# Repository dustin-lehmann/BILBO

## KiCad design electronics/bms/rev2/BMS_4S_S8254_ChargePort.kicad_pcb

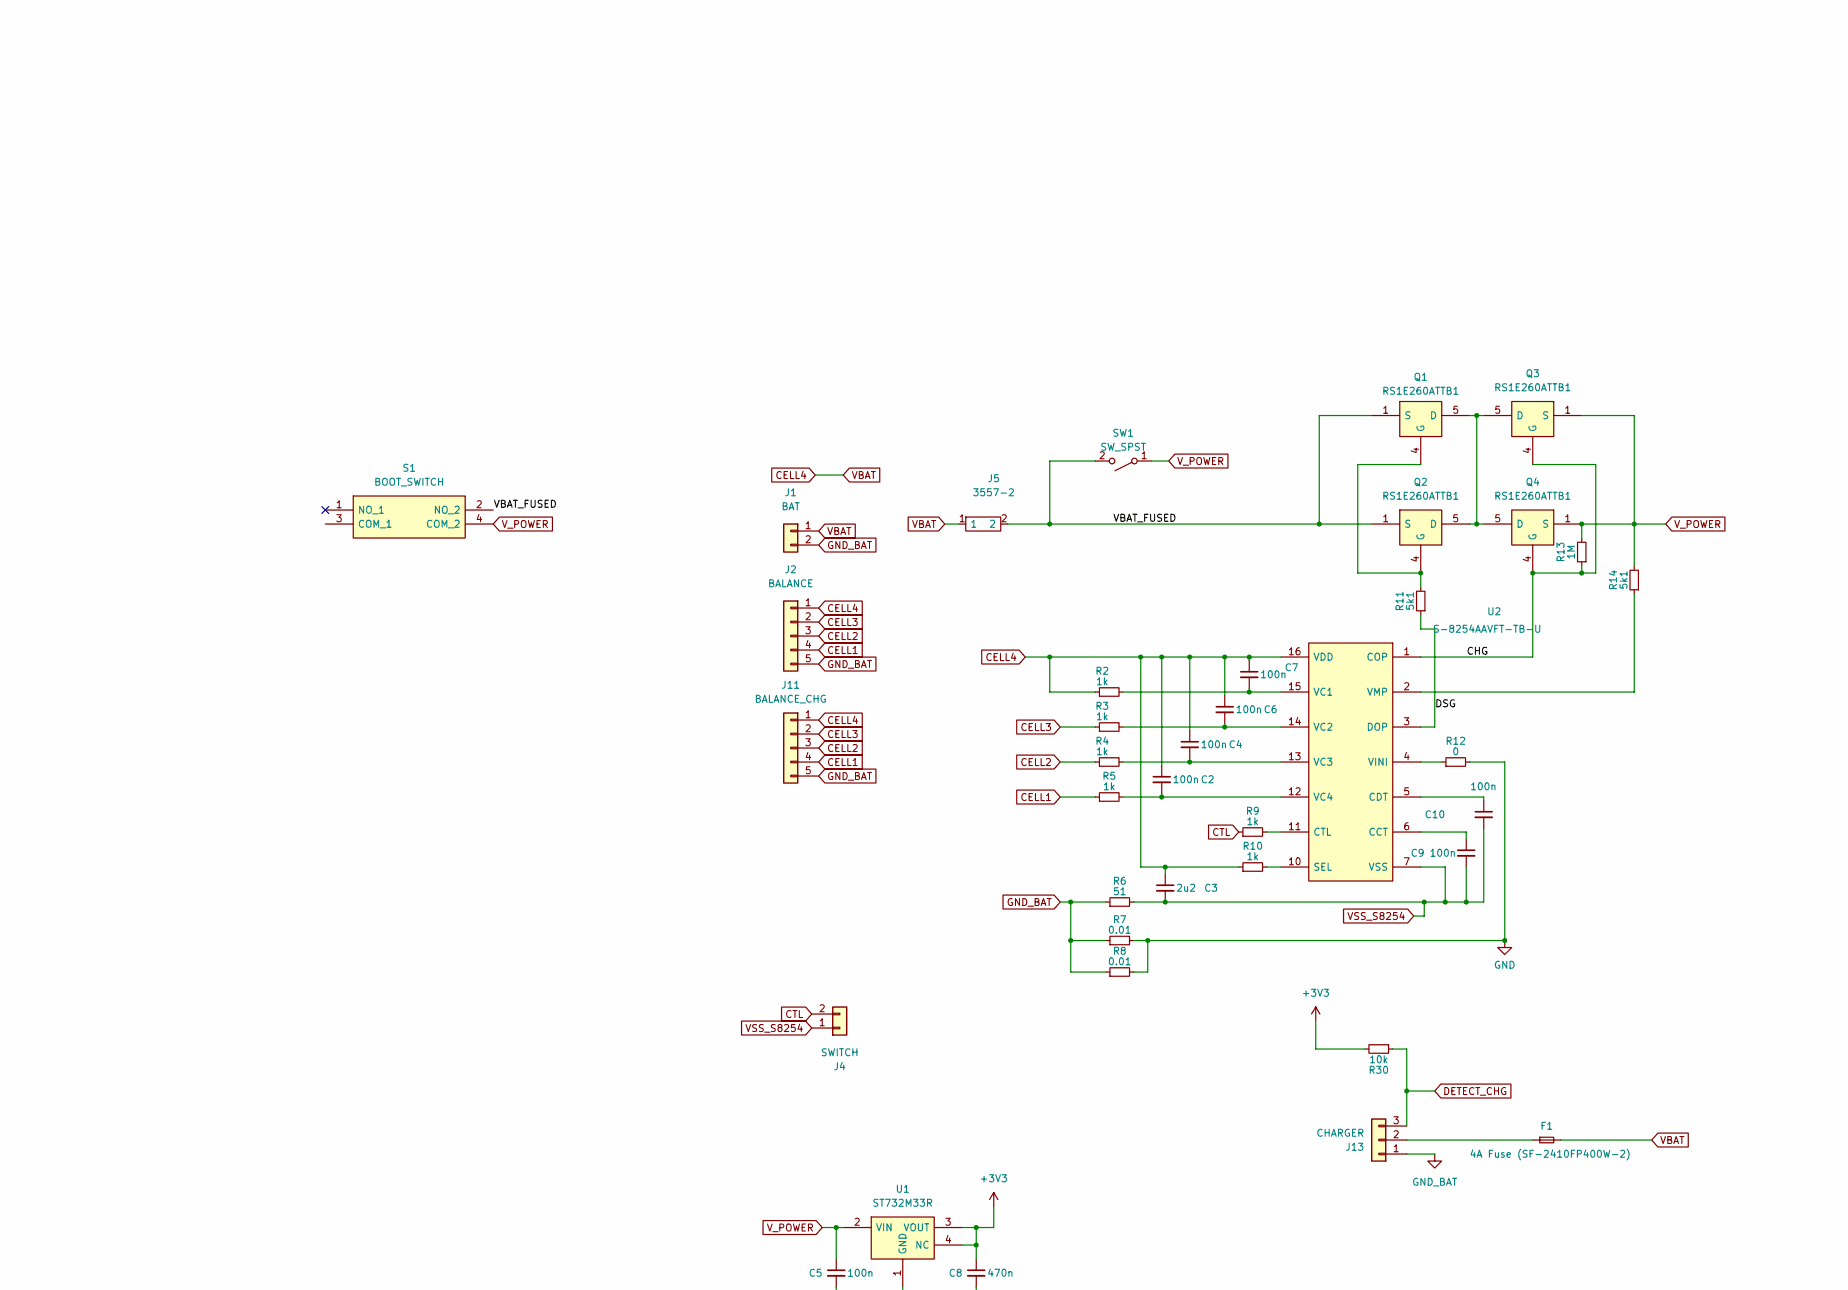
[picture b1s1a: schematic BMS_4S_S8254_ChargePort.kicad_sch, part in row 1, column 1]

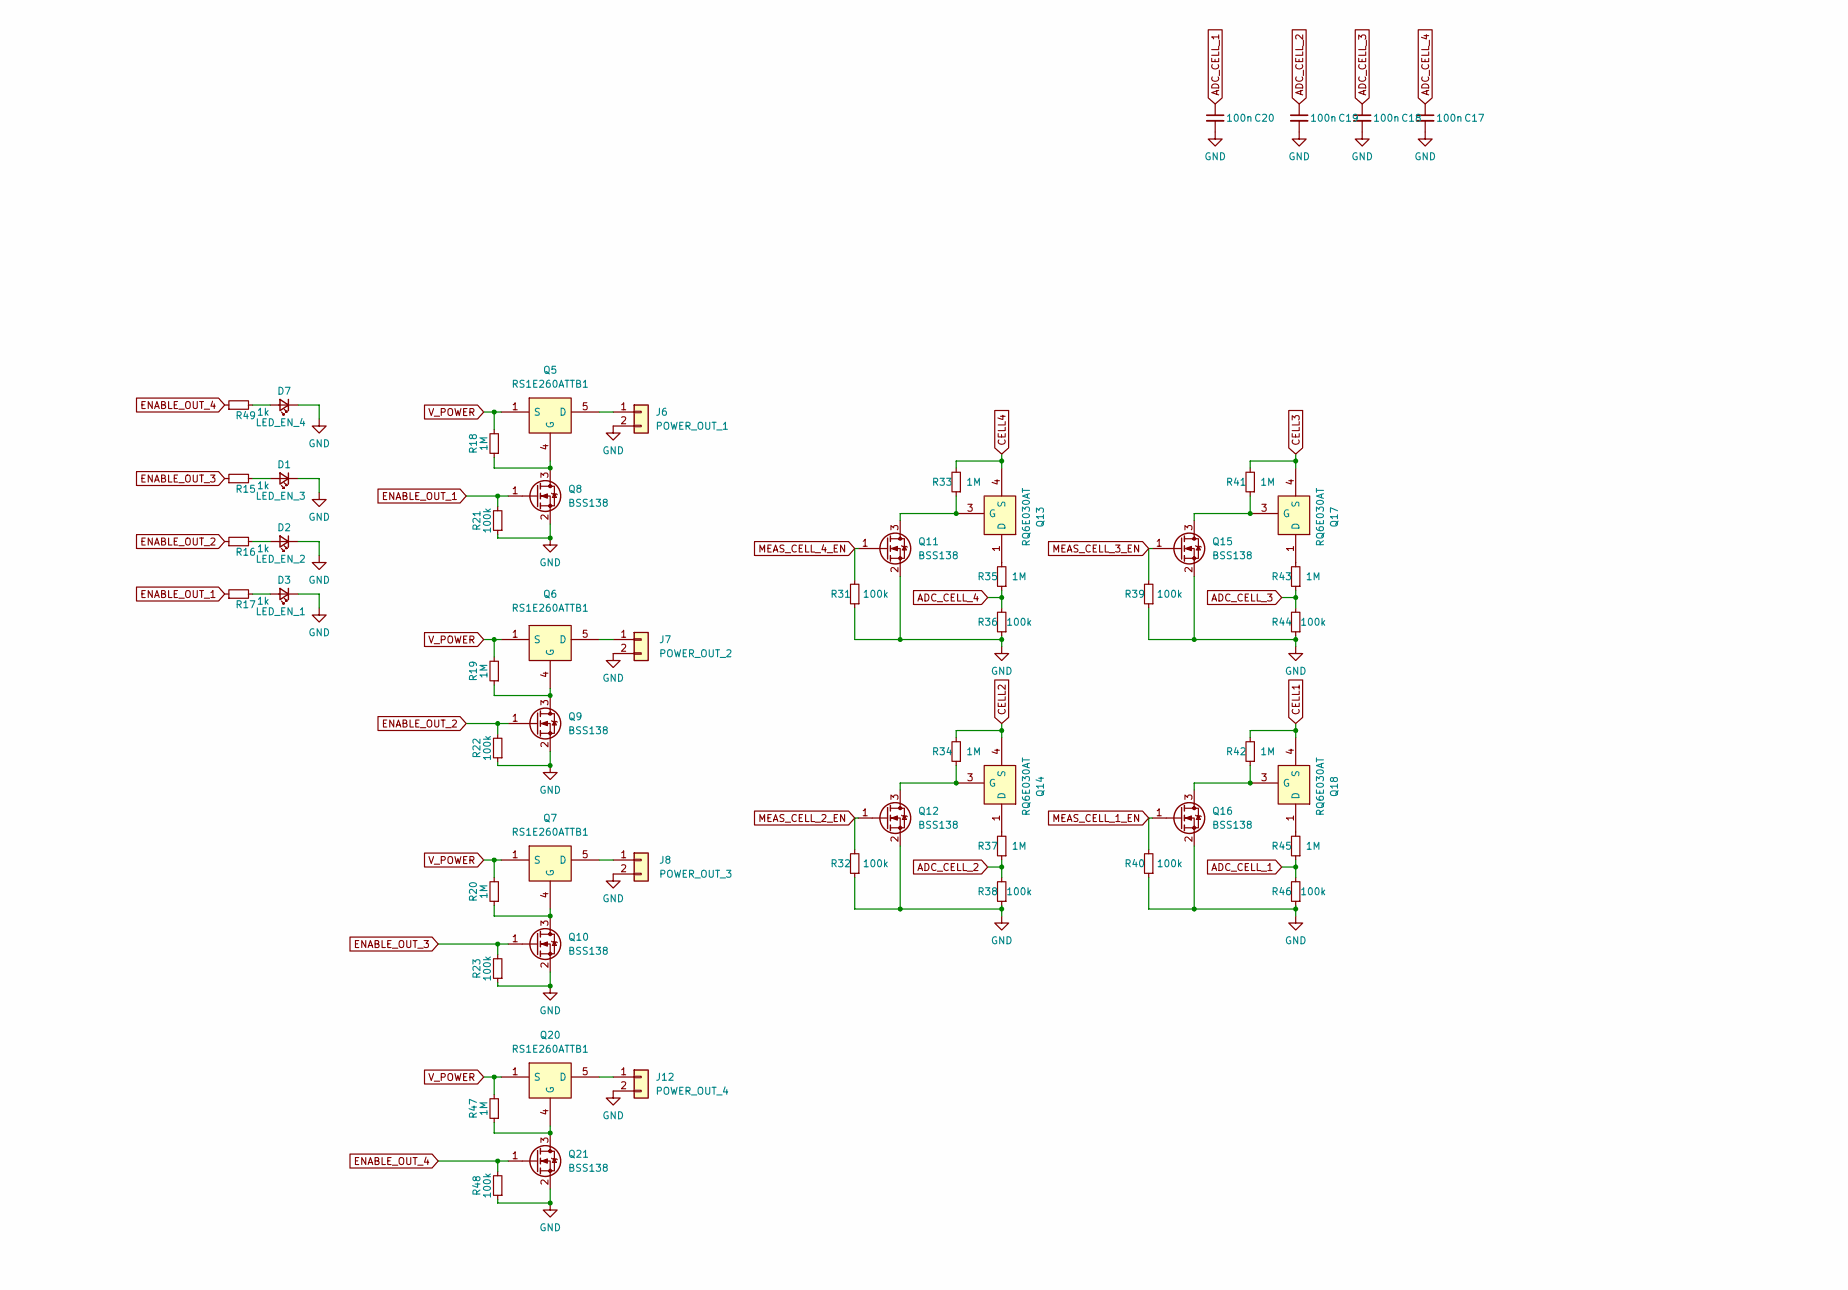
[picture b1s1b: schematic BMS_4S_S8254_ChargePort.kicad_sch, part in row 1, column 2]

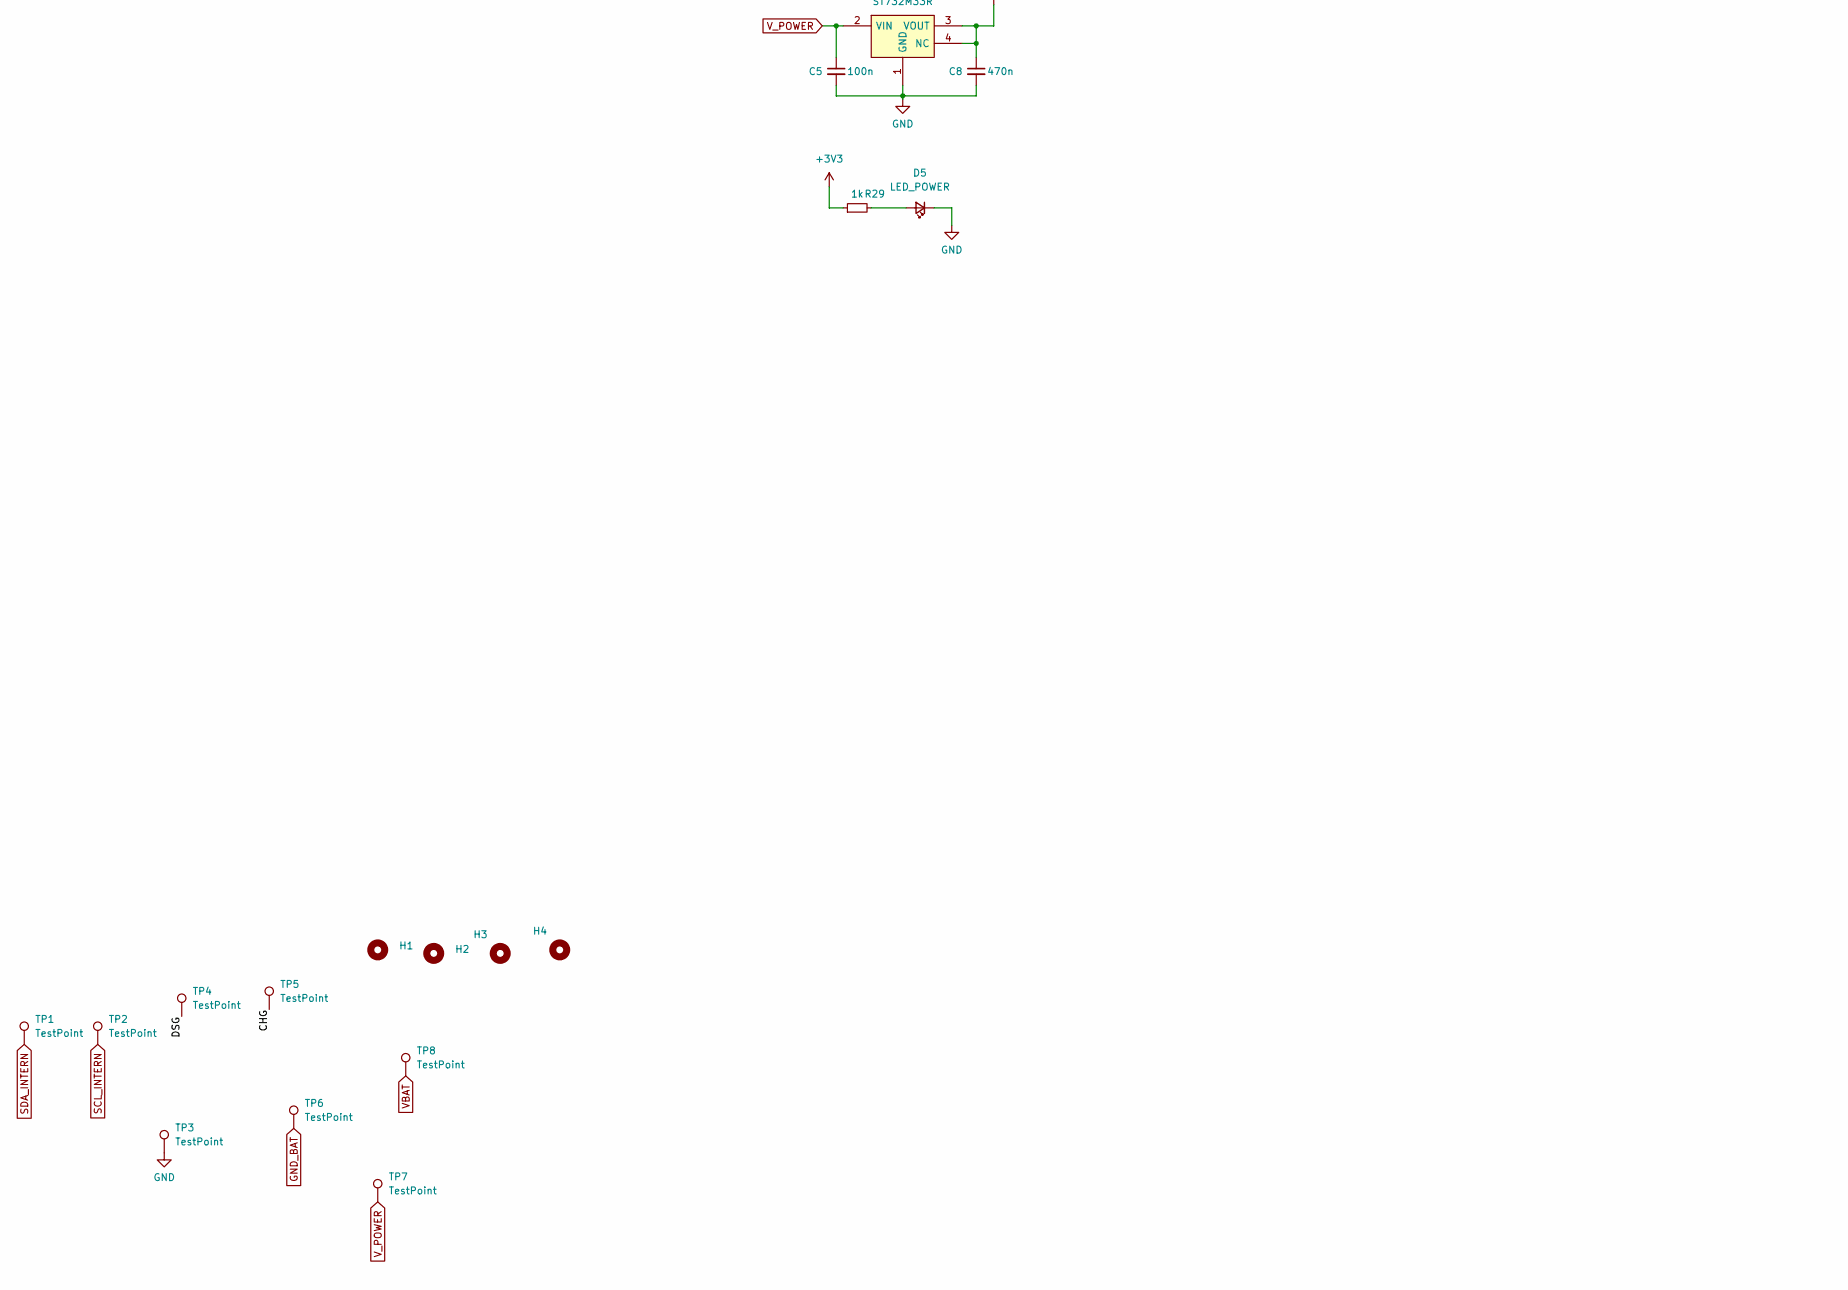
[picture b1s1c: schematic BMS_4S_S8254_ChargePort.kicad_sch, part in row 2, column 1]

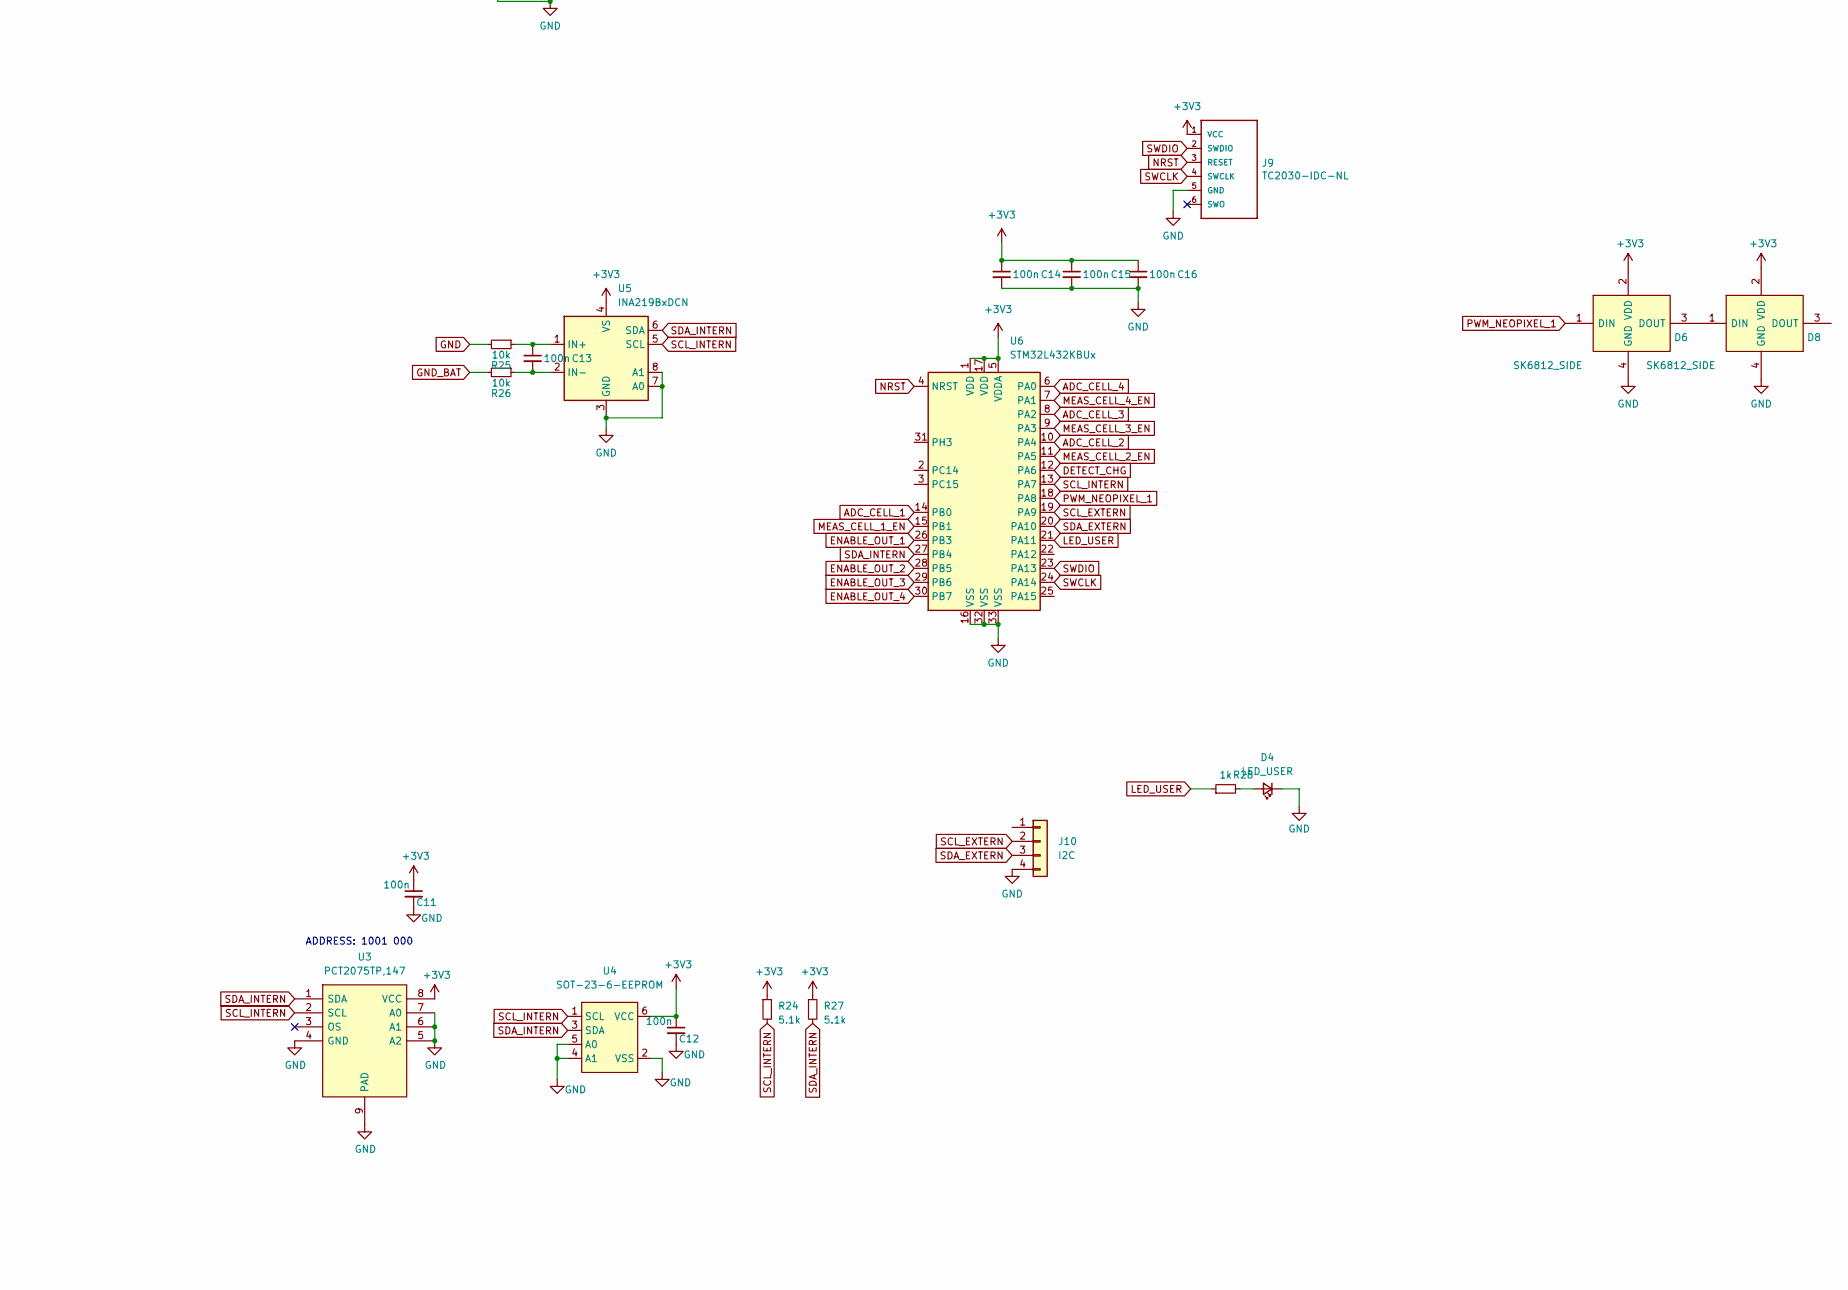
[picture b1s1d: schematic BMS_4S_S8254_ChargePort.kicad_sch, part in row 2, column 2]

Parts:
C2, C4, C5, C6, C7, C9, C10, C11, C12, C13, C14, C15, C16, C17, C18, C19, C20: 100n; C_0603_1608Metric
C3: 2u2; C_0805_2012Metric
C8: 470n; C_0603_1608Metric
D1: LED_EN_3; LED_0603_1608Metric
D2: LED_EN_2; LED_0603_1608Metric
D3: LED_EN_1; LED_0603_1608Metric
D4: LED_USER; LED_0603_1608Metric
D5: LED_POWER; LED_0603_1608Metric
D6, D8: SK6812_SIDE; SK6812SIDE; Manufacturer_Part_Number SK6812 SIDE
D7: LED_EN_4; LED_0603_1608Metric
F1: 4A Fuse (SF-2410FP400W-2); R_2512_6332Metric
H1, H2, H3, H4: MH_noPad_2.5
J1: BAT; AMASS_XT60PW-M
J2: BALANCE; JST_XH_S5B-XH-A_1x05_P2.50mm_Horizontal
J4: SWITCH; JST_GH_BM02B-GHS-TBT_1x02-1MP_P1.25mm_Vertical
J5: 3557-2; Mouser Part Number 534-3557-2
J6: POWER_OUT_1; 691322110002
J7: POWER_OUT_2; 691322110002
J8: POWER_OUT_3; 691322110002
J9: TC2030-IDC-NL; Tag-Connect_TC2030-IDC-NL_2x03_P1.27mm_Vertical
J10: I2C; JST_GH_BM04B-GHS-TBT_1x04-1MP_P1.25mm_Vertical
J11: BALANCE_CHG; JST_XH_S5B-XH-A_1x05_P2.50mm_Horizontal
J12: POWER_OUT_4; 691322110002
J13: CHARGER; AMASS_XT60IPW-M_1x03_P7.20mm_Horizontal
Q1, Q2, Q3, Q4, Q5, Q6, Q7, Q20: RS1E260ATTB1; Mouser Part Number 755-RS1E260ATTB1
Q8, Q9, Q10, Q11, Q12, Q15, Q16, Q21: BSS138; SOT-323_SC-70
Q13, Q14, Q17, Q18: RQ6E030AT; SOT95P280X100-6N; Mouser Part Number 755-RZQ045P01TR
R2, R3, R4, R5, R9, R10, R15, R16, R17, R28, R29, R49: 1k; R_0603_1608Metric
R6: 51; R_0603_1608Metric
R7, R8: 0.01; R_2512_6332Metric
R11, R14: 5k1; R_0603_1608Metric
R12: 0; R_0603_1608Metric
R13, R18, R19, R20, R33, R34, R35, R37, R41, R42, R43, R45, R47: 1M; R_0603_1608Metric
R21, R22, R23, R31, R32, R36, R38, R39, R40, R44, R46, R48: 100k; R_0603_1608Metric
R24, R27: 5.1k; R_0603_1608Metric
R25, R26, R30: 10k; R_0603_1608Metric
S1: BOOT_SWITCH; EVQPUA02K; Manufacturer_Part_Number 434123025826
SW1: SW_SPST; JST_GH_BM02B-GHS-TBT_1x02-1MP_P1.25mm_Vertical
TP1, TP2, TP3, TP4, TP5, TP6, TP7, TP8: TestPoint; TestPoint_Pad_D1.5mm
U1: ST732M33R; SOT95P280X145-5N; Mouser Part Number 511-ST732M33R
U2: S-8254AAVFT-TB-U; SOP65P640X110-16N; Mouser Part Number 628-S-8254AAVFT-TB-G
U3: PCT2075TP,147; SON50P300X200X80-9N; Mouser Part Number 771-PCT2075TP147
U4: SOT-23-6-EEPROM; SOT-23-6
U5: INA219BxDCN; SOT-23-8
U6: STM32L432KBUx; QFN-32-1EP_5x5mm_P0.5mm_EP3.45x3.45mm

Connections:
+3V3: C8.1, C11.1, C12.1, C14.1, C15.1, C16.1, D6.2 (VDD), D8.2 (VDD), J9.1 (VCC), R24.1, R27.1, R29.1, R30.2, U1.3 (VOUT), U1.4 (NC), U3.8 (VCC), U4.6 (VCC), U5.4 (VS), U6.1 (VDD), U6.5 (VDDA), U6.17 (VDD)
/CHG: Q3.4 (G), Q4.4 (G), R13.1, TP5.1, U2.1 (COP)
/DSG: R11.1, TP4.1, U2.3 (DOP)
/VBAT_FUSED: J5.2, J5.4, Q1.1 (S), Q1.2 (S), Q1.3 (S), Q2.1 (S), Q2.2 (S), Q2.3 (S), S1.2 (NO_2), SW1.2 (B)
ADC_CELL_1: C20.1, R45.1, R46.2, U6.14 (PB0)
ADC_CELL_2: C19.1, R37.1, R38.2, U6.10 (PA4)
ADC_CELL_3: C18.1, R43.1, R44.2, U6.8 (PA2)
ADC_CELL_4: C17.1, R35.1, R36.2, U6.6 (PA0)
CELL1: J2.4, J11.4, Q18.4 (S), R5.1, R42.2
CELL2: J2.3, J11.3, Q14.4 (S), R4.1, R34.2
CELL3: J2.2, J11.2, Q17.4 (S), R3.1, R41.2
CELL4: C2.1, C3.1, C4.1, C6.1, C7.1, F1.2, J1.1, J2.1, J5.1, J5.3, J11.1, Q13.4 (S), R2.1, R10.1, R33.2, TP8.1, U2.16 (VDD)
CTL: J4.2, R9.1
DETECT_CHG: J13.3, R30.1, U6.12 (PA6)
ENABLE_OUT_1: Q8.1 (G), R17.1, R21.2, U6.26 (PB3)
ENABLE_OUT_2: Q9.1 (G), R16.1, R22.2, U6.28 (PB5)
ENABLE_OUT_3: Q10.1 (G), R15.1, R23.2, U6.29 (PB6)
ENABLE_OUT_4: Q21.1 (G), R48.2, R49.1, U6.30 (PB7)
GND: C5.2, C8.2, C11.2, C12.2, C14.2, C15.2, C16.2, C17.2, C18.2, C19.2, C20.2, D1.1 (K), D2.1 (K), D3.1 (K), D4.1 (K), D5.1 (K), D6.4 (GND), D7.1 (K), D8.4 (GND), J6.2, J7.2, J8.2, J9.5 (GND), J10.4, J12.2, Q8.2 (S), Q9.2 (S), Q10.2 (S), Q11.2 (S), Q12.2 (S), Q15.2 (S), Q16.2 (S), Q21.2 (S), R7.2, R8.2, R12.2, R21.1, R22.1, R23.1, R25.2, R31.1, R32.1, R36.1, R38.1, R39.1, R40.1, R44.1, R46.1, R48.1, TP3.1, U1.1 (GND), U3.4 (GND), U3.5 (A2), U3.6 (A1), U3.7 (A0), U3.9 (PAD), U4.2 (VSS), U4.4 (A1), U4.5 (A0), U5.3 (GND), U5.7 (A0), U5.8 (A1), U6.16 (VSS), U6.32 (VSS), U6.33 (VSS)
GND_BAT: J1.2, J2.5, J11.5, J13.1, R6.1, R7.1, R8.1, R26.2, TP6.1
LED_USER: R28.1, U6.21 (PA11)
MEAS_CELL_1_EN: Q16.1 (G), R40.2, U6.15 (PB1)
MEAS_CELL_2_EN: Q12.1 (G), R32.2, U6.11 (PA5)
MEAS_CELL_3_EN: Q15.1 (G), R39.2, U6.9 (PA3)
MEAS_CELL_4_EN: Q11.1 (G), R31.2, U6.7 (PA1)
NRST: J9.3 (RESET), U6.4 (NRST)
unnamed: D1.2 (A), R15.2
unnamed: D2.2 (A), R16.2
unnamed: D3.2 (A), R17.2
unnamed: D4.2 (A), R28.2
unnamed: D5.2 (A), R29.2
unnamed: D6.3 (DOUT), D8.1 (DIN)
unnamed: D7.2 (A), R49.2
unnamed: J6.1, Q5.5 (D), Q5.6 (D), Q5.7 (D), Q5.8 (D), Q5.9 (D)
unnamed: J7.1, Q6.5 (D), Q6.6 (D), Q6.7 (D), Q6.8 (D), Q6.9 (D)
unnamed: J8.1, Q7.5 (D), Q7.6 (D), Q7.7 (D), Q7.8 (D), Q7.9 (D)
unnamed: J12.1, Q20.5 (D), Q20.6 (D), Q20.7 (D), Q20.8 (D), Q20.9 (D)
unnamed: F1.1, J13.2
unnamed: Q1.5 (D), Q1.6 (D), Q1.7 (D), Q1.8 (D), Q1.9 (D), Q2.5 (D), Q2.6 (D), Q2.7 (D), Q2.8 (D), Q2.9 (D), Q3.5 (D), Q3.6 (D), Q3.7 (D), Q3.8 (D), Q3.9 (D), Q4.5 (D), Q4.6 (D), Q4.7 (D), Q4.8 (D), Q4.9 (D)
unnamed: Q1.4 (G), Q2.4 (G), R11.2
unnamed: Q5.4 (G), Q8.3 (D), R18.1
unnamed: Q6.4 (G), Q9.3 (D), R19.1
unnamed: Q7.4 (G), Q10.3 (D), R20.1
unnamed: Q11.3 (D), Q13.3 (G), R33.1
unnamed: Q12.3 (D), Q14.3 (G), R34.1
unnamed: Q13.1 (D), Q13.2 (D), Q13.5 (D), Q13.6 (D), R35.2
unnamed: Q14.1 (D), Q14.2 (D), Q14.5 (D), Q14.6 (D), R37.2
unnamed: Q15.3 (D), Q17.3 (G), R41.1
unnamed: Q16.3 (D), Q18.3 (G), R42.1
unnamed: Q17.1 (D), Q17.2 (D), Q17.5 (D), Q17.6 (D), R43.2
unnamed: Q18.1 (D), Q18.2 (D), Q18.5 (D), Q18.6 (D), R45.2
unnamed: Q20.4 (G), Q21.3 (D), R47.1
unnamed: C9.1, U2.6 (CCT)
unnamed: C10.1, U2.5 (CDT)
unnamed: R9.2, U2.11 (CTL)
unnamed: R10.2, U2.10 (SEL)
unnamed: C7.2, R2.2, U2.15 (VC1)
unnamed: C6.2, R3.2, U2.14 (VC2)
unnamed: C4.2, R4.2, U2.13 (VC3)
unnamed: C2.2, R5.2, U2.12 (VC4)
unnamed: R12.1, U2.4 (VINI)
unnamed: R14.1, U2.2 (VMP)
unnamed: C13.1, R25.1, U5.1 (IN+)
unnamed: C13.2, R26.1, U5.2 (IN-)
PWM_NEOPIXEL_1: D6.1 (DIN), U6.18 (PA8)
SCL_EXTERN: J10.2, U6.19 (PA9)
SCL_INTERN: R24.2, TP2.1, U3.2 (SCL), U4.1 (SCL), U5.5 (SCL), U6.13 (PA7)
SDA_EXTERN: J10.3, U6.20 (PA10)
SDA_INTERN: R27.2, TP1.1, U3.1 (SDA), U4.3 (SDA), U5.6 (SDA), U6.27 (PB4)
SWCLK: J9.4 (SWCLK), U6.24 (PA14)
SWDIO: J9.2 (SWDIO), U6.23 (PA13)
VSS_S8254: C3.2, C9.2, C10.2, J4.1, R6.2, U2.7 (VSS)
V_POWER: C5.1, Q3.1 (S), Q3.2 (S), Q3.3 (S), Q4.1 (S), Q4.2 (S), Q4.3 (S), Q5.1 (S), Q5.2 (S), Q5.3 (S), Q6.1 (S), Q6.2 (S), Q6.3 (S), Q7.1 (S), Q7.2 (S), Q7.3 (S), Q20.1 (S), Q20.2 (S), Q20.3 (S), R13.2, R14.2, R18.2, R19.2, R20.2, R47.2, S1.4 (COM_2), SW1.1 (A), TP7.1, U1.2 (VIN)

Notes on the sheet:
ADDRESS: 1001 000

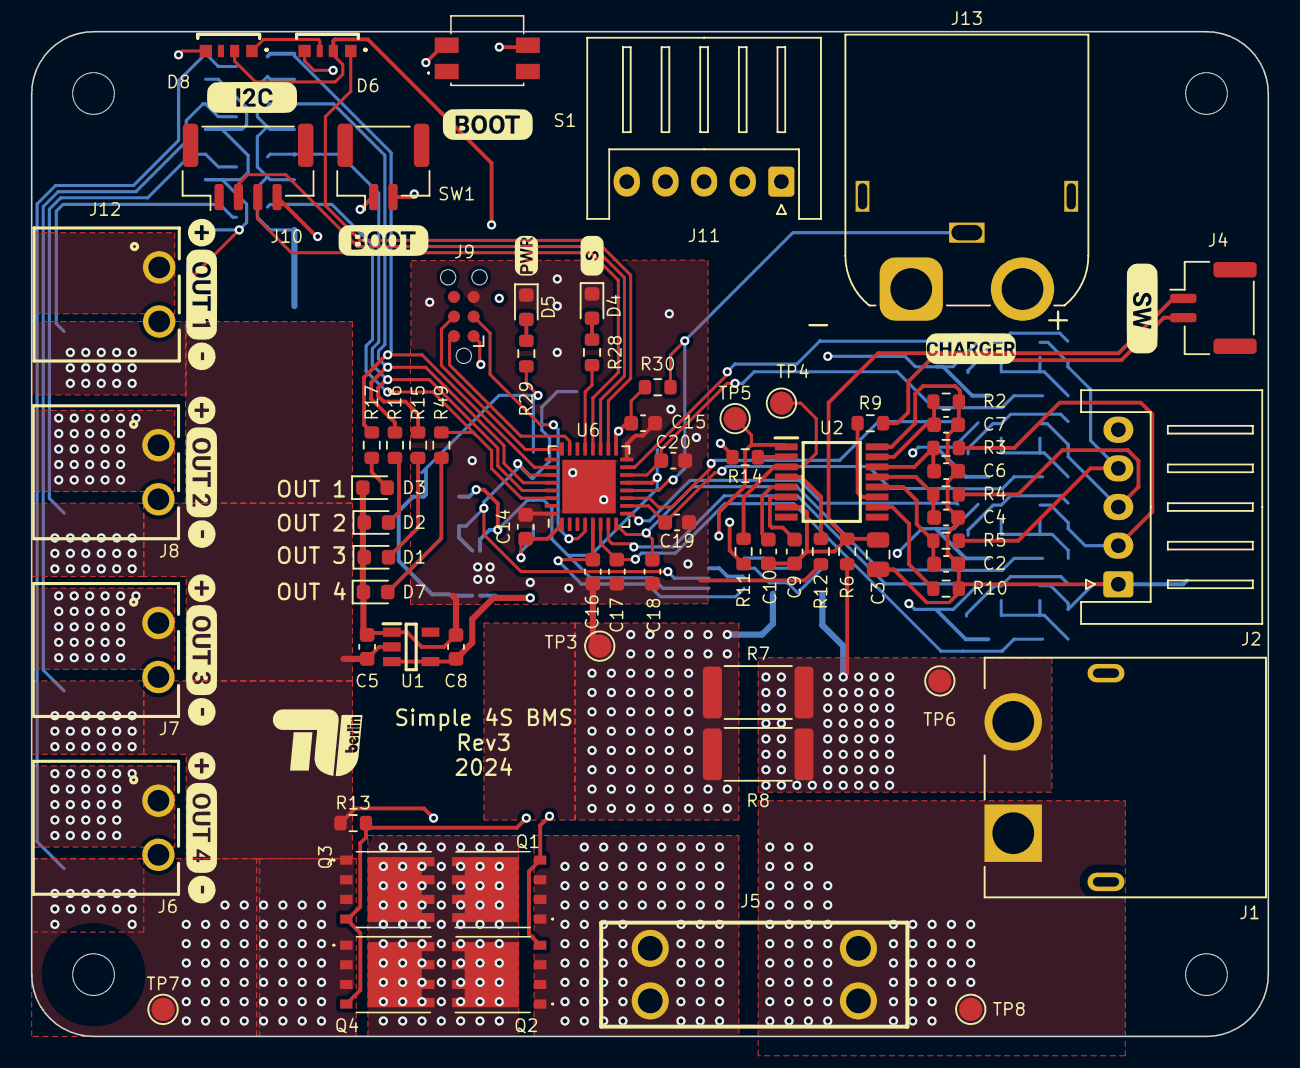
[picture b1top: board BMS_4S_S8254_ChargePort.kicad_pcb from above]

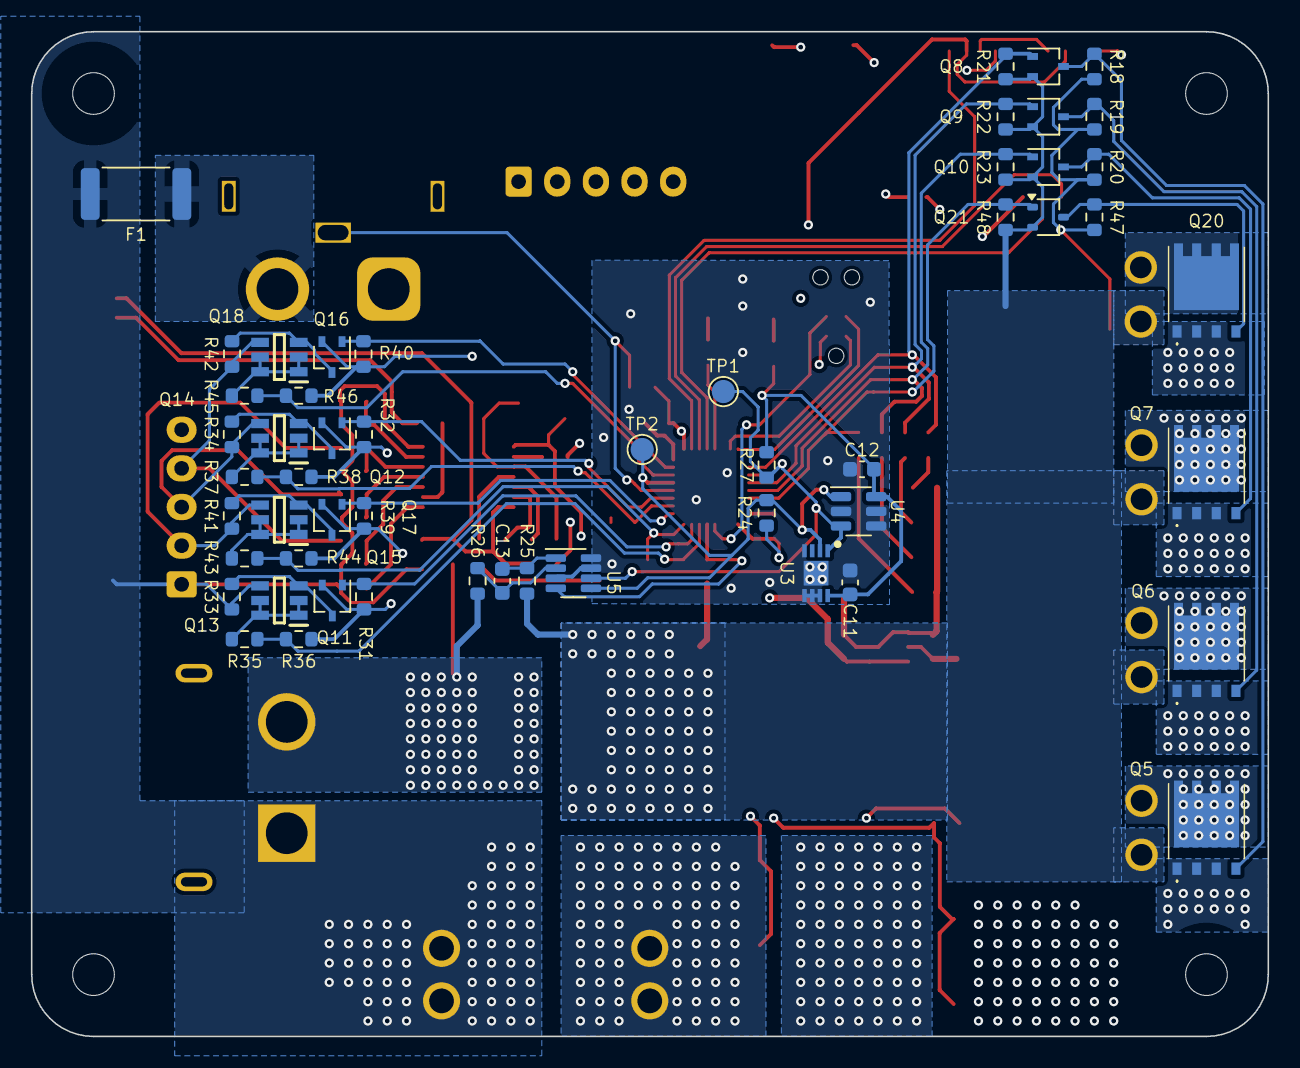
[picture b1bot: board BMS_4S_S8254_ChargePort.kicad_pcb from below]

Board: 4 copper layers, 80.0 x 65.0 mm, 128 parts (53 on the bottom side), 73 nets.

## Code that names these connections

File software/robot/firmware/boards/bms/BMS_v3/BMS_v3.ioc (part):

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Mcu.Name=STM32L432K(B-C)Ux
Mcu.Package=UFQFPN32
Mcu.UserName=STM32L432KBUx
PA1.GPIOParameters=GPIO_Label
PA1.GPIO_Label=ENABLE_MEAS_1
PA1.Signal=GPIO_Output
PA11.GPIOParameters=GPIO_Label
PA11.GPIO_Label=LED_USER
PA11.Signal=GPIO_Output
PA13\ (JTMS-SWDIO).Mode=Serial_Wire
PA13\ (JTMS-SWDIO).Signal=SYS_JTMS-SWDIO
PA14\ (JTCK-SWCLK).Mode=Serial_Wire
PA14\ (JTCK-SWCLK).Signal=SYS_JTCK-SWCLK
PA15\ (JTDI).Signal=GPIO_Analog
PA4.GPIOParameters=GPIO_Label
PA4.GPIO_Label=ADC_CELL_3
PA4.Signal=ADCx_IN9
PA5.GPIOParameters=GPIO_Label
PA5.GPIO_Label=ENABLE_MEAS_3
PA5.Signal=GPIO_Output
PA6.GPIOParameters=GPIO_PuPd,GPIO_Label
PA6.GPIO_Label=DETECT_CHG
PA6.GPIO_PuPd=GPIO_PULLUP
PA6.Signal=GPIO_Input
PB0.GPIOParameters=GPIO_Label
PB0.GPIO_Label=ADC_CELL_4
PB0.Signal=ADCx_IN15
PB1.GPIOParameters=GPIO_Label
PB1.GPIO_Label=ENABLE_MEAS_4
PB1.Signal=GPIO_Output
PB3\ (JTDO-TRACESWO).GPIOParameters=GPIO_Label
PB3\ (JTDO-TRACESWO).GPIO_Label=OUT_2
PB3\ (JTDO-TRACESWO).Signal=GPIO_Output
PB5.GPIOParameters=GPIO_Label
PB5.GPIO_Label=OUT_1
PB5.Signal=GPIO_Output
PB6.GPIOParameters=GPIO_Label
PB6.GPIO_Label=OUT_3
PB6.Signal=GPIO_Output
PB7.GPIOParameters=GPIO_Label
PB7.GPIO_Label=OUT_4
PB7.Signal=GPIO_Output
RCC.HSE_VALUE=8000000
RCC.SYSCLKFreq_VALUE=16000000
RCC.SYSCLKSource=RCC_SYSCLKSOURCE_HSI
board=custom

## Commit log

2024-12-13 test push
2024-12-13 test github readme background image
2025-02-14 added add_mov and set_mode support
2025-02-18 updated CLI
2025-02-18 add experiment support
2025-02-18 add sample experiment
2025-02-20 add pause/continue support for navigation control
2025-02-20 add simple marker visualization
2025-02-20 add alpha=0 for no longer visible aruco markers
2025-02-21 changed babylon visualization
2025-02-21 added big version of bilbo
2025-02-26 readibility update
2025-02-26 Reworked the thread worker to allow multiple starts
2025-02-26 simultaneos agent measurement updates
2025-02-27 Cleaned up the repo
2025-02-27 Added FRODO Hardware and Software to the repo
2025-02-27 Added FRODO o\Logo
2025-02-27 Removed unnecessary code
2025-02-27 added experiment log base
2025-02-28 fix local import error
2025-02-28 add v, psi_dot, time to log data
2025-02-28 add logging marker support with audio signals
